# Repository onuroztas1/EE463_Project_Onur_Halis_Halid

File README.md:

# EE463_Project_Onur_Halis_Halid

Google Docs Link:
https://docs.google.com/document/d/1aUbiogccKc2OzVAZYlh6jZ1xVPGB8dJCKc63r1MVhF4/edit?usp=sharing

Google Slides Link:
https://docs.google.com/presentation/d/1uwI3XgHL8aJ05a1YgI6h8vrzoWMBWJBdzZAcA0tdUn0/edit?usp=sharing

Final Report Link: https://docs.google.com/document/d/186Mo9F-AtZxF1AbLLBHefO2YgB5pBUfvJb4pfUX1ARI/edit?usp=sharing

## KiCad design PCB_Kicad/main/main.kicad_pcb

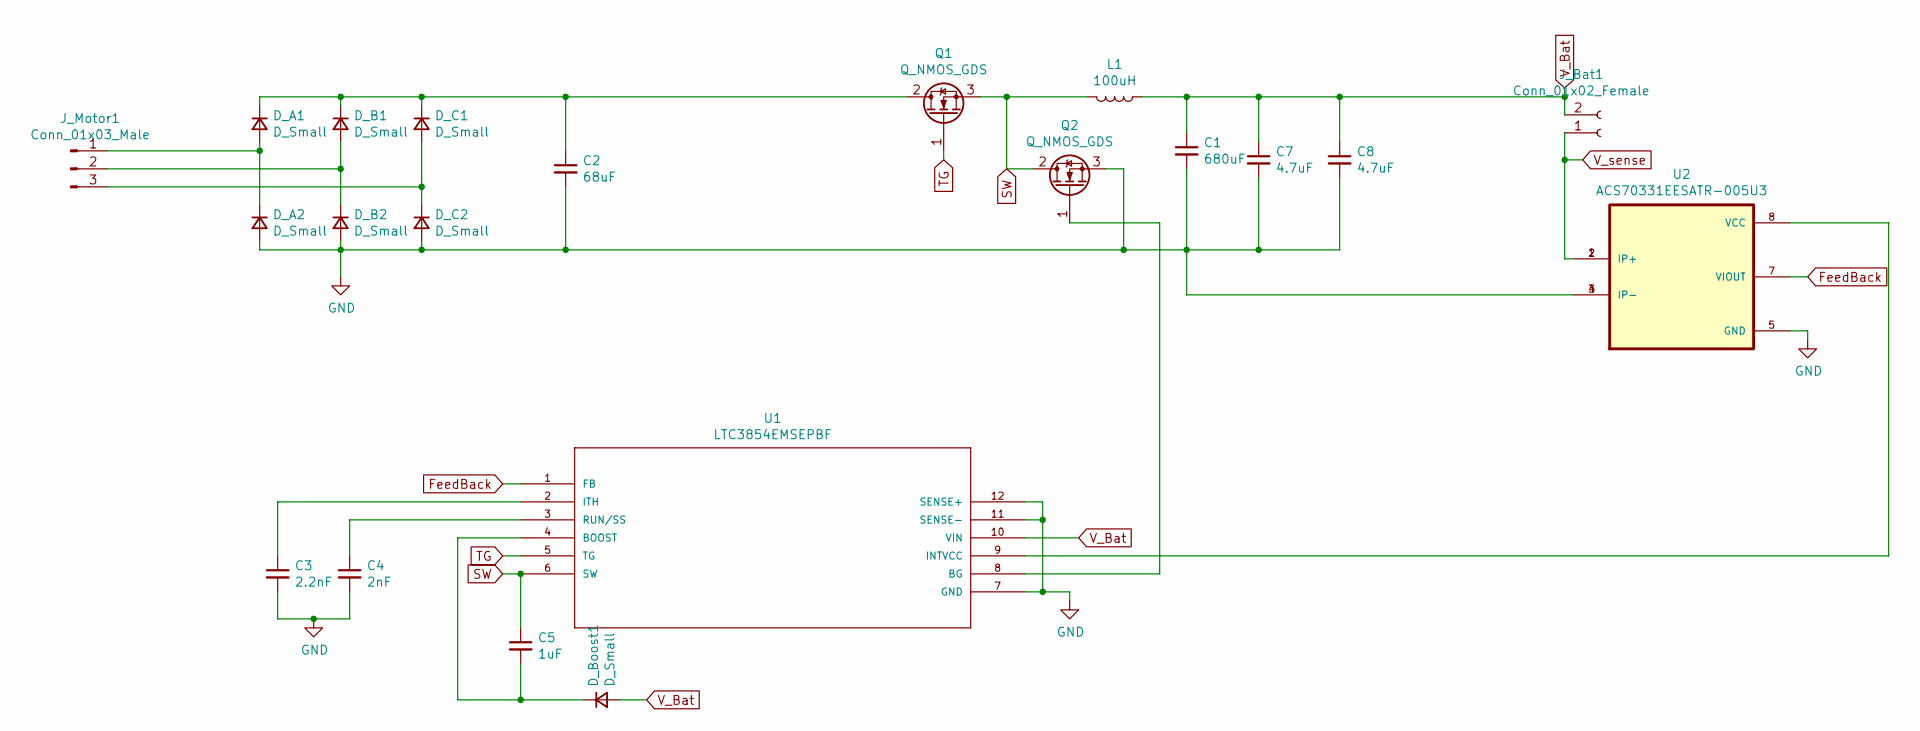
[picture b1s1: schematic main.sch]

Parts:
C1: 680uF; CP_Elec_10x7.9
C2: 68uF; CP_Radial_D18.0mm_P7.50mm
C3: 2.2nF; C_1206_3216Metric
C4: 2nF; C_1206_3216Metric
C5: 1uF; CP_Elec_8x10
C7, C8: 4.7uF; C_0805_2012Metric
D_A1, D_A2: D_Small; D_SMB
D_B1, D_B2: D_Small; D_SMB
D_Boost1: D_Small; D_SMB
D_C1, D_C2: D_Small; D_SMB
J_Bat1: Conn_01x02_Female; TerminalBlock_Altech_AK300-2_P5.00mm
J_Motor1: Conn_01x03_Male; TerminalBlock_Altech_AK300-3_P5.00mm
L1: 100uH; L_Wuerth_HCM-1390
Q1, Q2: Q_NMOS_GDS; TO-220-3_Vertical
U1: LTC3854EMSEPBF; MSOP-12-1EP_3x4mm_P0.65mm_EP1.65x2.85mm; MANUFACTURER_PART_NUMBER ltc3854emse#pbf
U2: ACS70331EESATR-005U3; SOIC-8-1EP_3.9x4.9mm_P1.27mm_EP2.29x3mm; PARTREV 2

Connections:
FeedBack: U1.1 (FB), U2.7 (VIOUT)
GND: C1.2, C2.2, C3.2, C4.2, C7.2, C8.2, D_A2.2 (A), D_B2.2 (A), D_C2.2 (A), Q2.3 (S), U1.7 (GND), U1.11 (SENSE-), U1.12 (SENSE+), U2.3 (IP-), U2.4 (IP-), U2.5 (GND)
unnamed: C2.1, D_A1.1 (K), D_B1.1 (K), D_C1.1 (K), Q1.2 (D)
unnamed: C3.1, U1.2 (ITH)
unnamed: C4.1, U1.3 (RUN/SS)
unnamed: C5.2, D_Boost1.1 (K), U1.4 (BOOST)
unnamed: D_A1.2 (A), D_A2.1 (K), J_Motor1.1
unnamed: D_B1.2 (A), D_B2.1 (K), J_Motor1.2
unnamed: D_C1.2 (A), D_C2.1 (K), J_Motor1.3
unnamed: Q2.1 (G), U1.8 (BG)
unnamed: U1.9 (INTVCC), U2.8 (VCC)
SW: C5.1, L1.2, Q1.3 (S), Q2.2 (D), U1.6 (SW)
TG: Q1.1 (G), U1.5 (TG)
V_Bat: C1.1, C7.1, C8.1, D_Boost1.2 (A), J_Bat1.2, L1.1, U1.10 (VIN)
V_sense: J_Bat1.1, U2.1 (IP+), U2.2 (IP+)

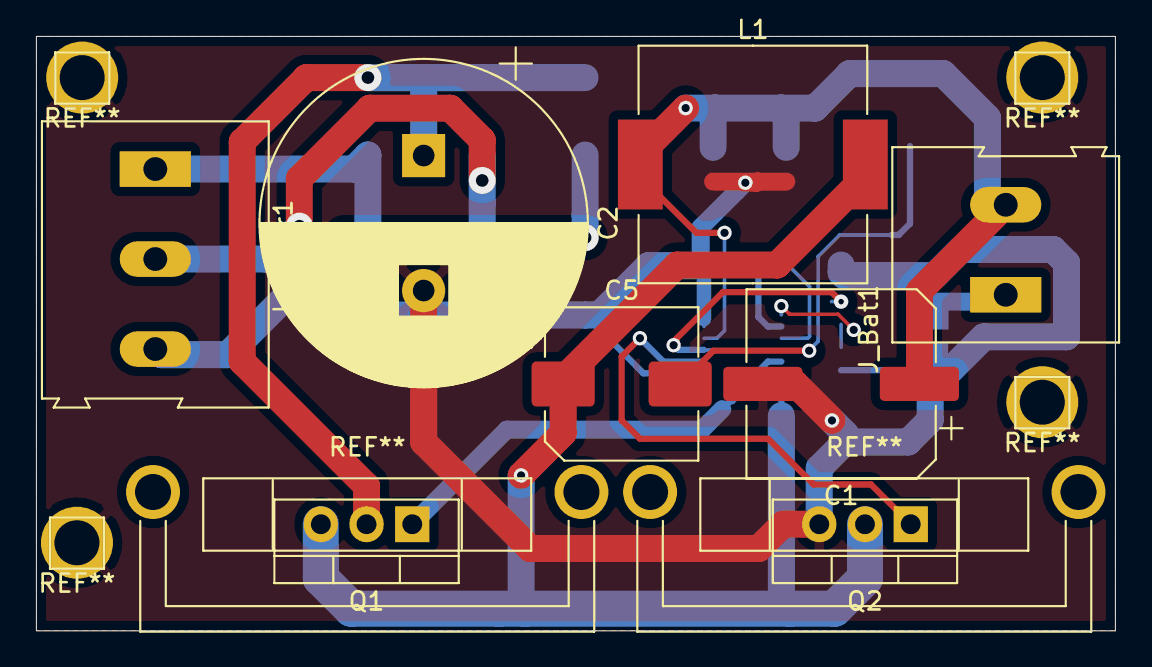
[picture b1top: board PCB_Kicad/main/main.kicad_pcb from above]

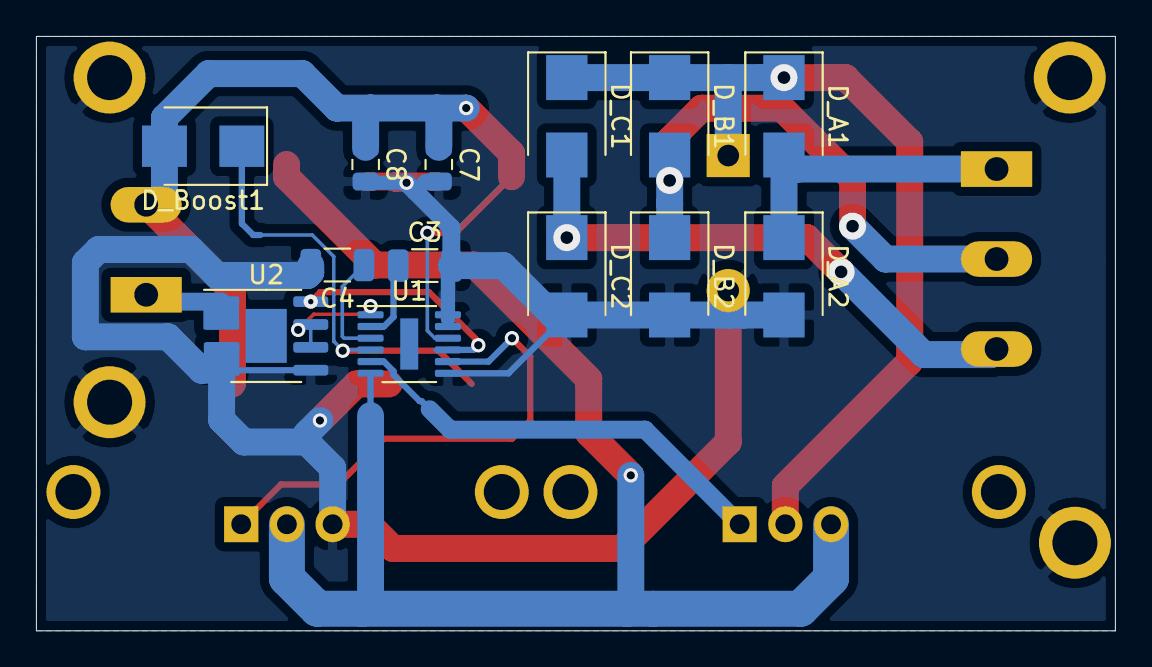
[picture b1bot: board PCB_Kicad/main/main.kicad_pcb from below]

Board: 2 copper layers, 59.9 x 33.0 mm, 21 parts (13 on the bottom side), 15 nets.

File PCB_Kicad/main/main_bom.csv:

"Source:","C:\Users\karab\OneDrive\Documents\GitHub\EE463_Project_Onur_Halis_Halid\PCB_Kicad\main\main.sch"
"Date:","12.01.2021 22:29:58"
"Tool:","Eeschema (5.1.8)-1"
"Component Count:","22"
"Ref","Value","Footprint","Datasheet","Manufacturer","Vendor"
"C1","680uF","Capacitor_SMD:CP_Elec_6.3x7.7","~","",""
"C2","68uF","Capacitor_SMD:CP_Elec_6.3x7.7","~","",""
"C3","2.2nF","Capacitor_SMD:C_1206_3216Metric","~","",""
"C4","2nF","Capacitor_SMD:C_1206_3216Metric","~","",""
"C5","1uF","Capacitor_SMD:CP_Elec_6.3x7.7","~","",""
"C6","68uF","Capacitor_SMD:CP_Elec_6.3x7.7","~","",""
"C7","4.7uF","Capacitor_SMD:C_2225_5664Metric_Pad1.80x6.60mm_HandSolder","~","",""
"C8","4.7uF","Capacitor_SMD:C_2225_5664Metric_Pad1.80x6.60mm_HandSolder","~","",""
"D_A1","D_Small","Diode_SMD:D_SMB","~","",""
"D_A2","D_Small","Diode_SMD:D_SMB","~","",""
"D_B1","D_Small","Diode_SMD:D_SMB","~","",""
"D_B2","D_Small","Diode_SMD:D_SMB","~","",""
"D_Boost1","D_Small","Diode_SMD:D_SMB","~","",""
"D_C1","D_Small","Diode_SMD:D_SMB","~","",""
"D_C2","D_Small","Diode_SMD:D_SMB","~","",""
"J_Bat1","Conn_01x02_Female","TerminalBlock:TerminalBlock_Altech_AK300-2_P5.00mm","~","",""
"J_Motor1","Conn_01x03_Male","TerminalBlock:TerminalBlock_Altech_AK300-3_P5.00mm","~","",""
"L1","100uH","Inductor_SMD:L_Wuerth_HCM-1390","~","",""
"Q1","Q_NMOS_GDS","Package_TO_SOT_THT:TO-220-3_Vertical","~","",""
"Q2","Q_NMOS_GDS","Package_TO_SOT_THT:TO-220-3_Vertical","~","",""
"U1","LTC3854EMSEPBF","Package_SO:MSOP-12-1EP_3x4mm_P0.65mm_EP1.65x2.85mm","","",""
"U2","ACS70331EESATR-005U3","Package_SO:SOIC-8-1EP_3.9x4.9mm_P1.27mm_EP2.29x3mm","","",""

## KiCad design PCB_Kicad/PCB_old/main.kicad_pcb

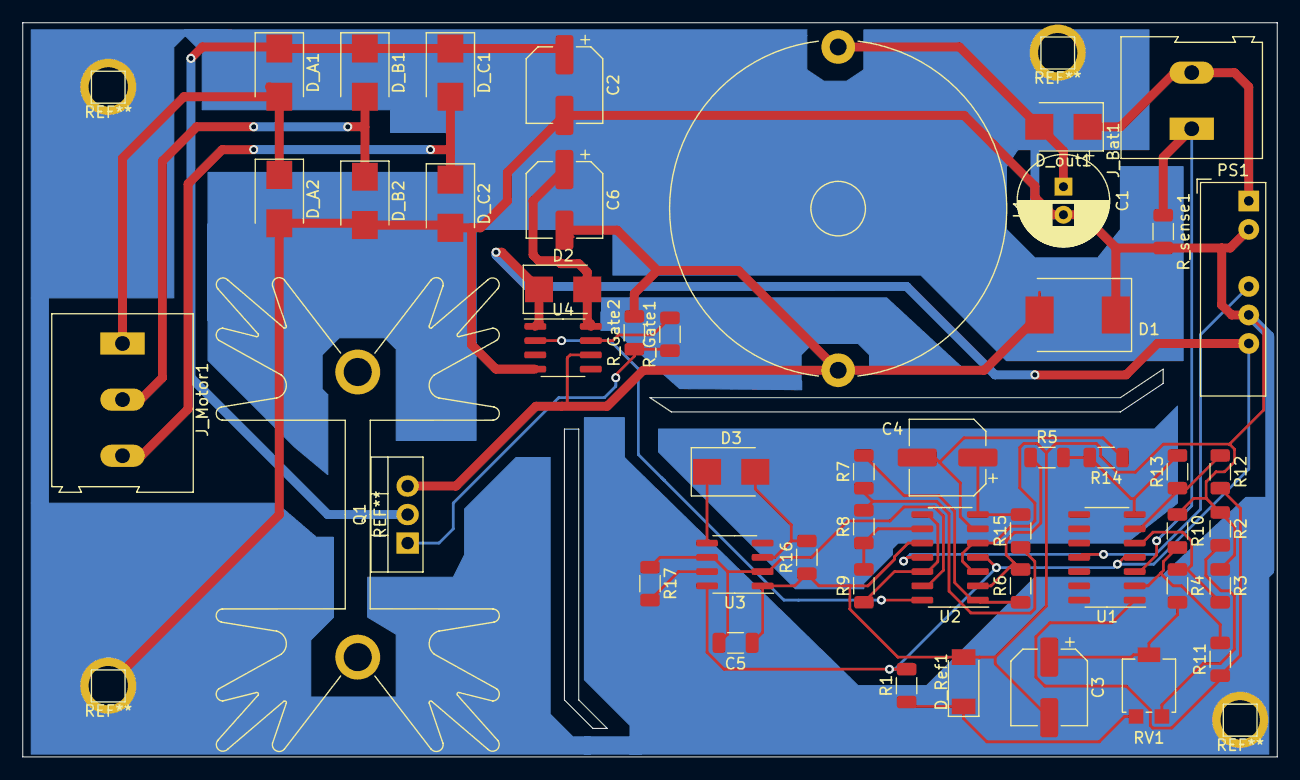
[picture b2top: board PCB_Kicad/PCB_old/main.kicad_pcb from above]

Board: 2 copper layers, 111.8 x 65.4 mm, 47 parts (0 on the bottom side), 34 nets.

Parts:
C1: 1mF; CP_Radial_D8.0mm_P2.50mm
C2: 100uF; CP_Elec_6.3x7.7
C3, C4, C6: C_Small; CP_Elec_6.3x7.7
C5: C_Small; C_1206_3216Metric
D1: DIODE; D_SMC
D2, D3: DIODE; D_SMB
D_A1, D_A2: D_Small; D_SMB
D_B1, D_B2: D_Small; D_SMB
D_C1, D_C2: D_Small; D_SMB
D_Ref1: D_Zener_Small; D_SOD-128
D_out1: D_Schottky; D_SMB
J_Bat1: Conn_01x02_Female; TerminalBlock_Altech_AK300-2_P5.00mm
J_Motor1: Conn_01x03_Male; TerminalBlock_Altech_AK300-3_P5.00mm
L1: L; L_Radial_D29.8mm_P28.80mm_muRATA_1400series
PS1: IA2412S; Converter_DCDC_XP_POWER-IAxxxxS_THT
Q1: Q_NMOS_GDS; TO-220-3_Vertical
R1, R2, R3, R4, R5, R6, R7, R8, R9, R10, R11, R12, R13, R14, R15, R16, R17: R_Small_US; R_1206_3216Metric
RV1: R_POT_TRIM_US; Potentiometer_Bourns_3314G_Vertical
R_Gate1, R_Gate2: R_Small_US; R_1206_3216Metric
R_sense1: R_Small_US; R_1206_3216Metric
U1, U2: TL084; SOIC-14_3.9x8.7mm_P1.27mm
U3: NA555D; SOIC-8_3.9x4.9mm_P1.27mm
U4: FAN7371; SOIC-8_3.9x4.9mm_P1.27mm

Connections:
+12V: D2.1, PS1.6, R1.2, U1.4, U2.4, U3.8, U4.1
-12V: PS1.4, U1.11, U2.11
GND: C1.2, C2.2, C3.2, C5.1, D1.1, D_A2.2, D_B2.2, D_C2.2, D_Ref1.2, PS1.2, PS1.5, R2.1, R3.1, R10.1, R16.1, R_sense1.2, U2.3, U2.5, U2.10, U3.1, U4.4
unnamed: C1.1, D_out1.2, L1.1
unnamed: C2.1, D_A1.1, D_B1.1, D_C1.1, Q1.2
unnamed: C3.1, R4.2, RV1.2
unnamed: C4.1, R15.2, U2.7
unnamed: C4.2, R14.1, U2.6
unnamed: C6.1, D2.2, U4.8
unnamed: C6.2, D1.2, L1.2, Q1.3, R_Gate2.2, U4.6
unnamed: D3.1, U3.5
unnamed: D3.2, R16.2, U3.3
unnamed: D_A1.2, D_A2.1, J_Motor1.1
unnamed: D_B1.2, D_B2.1, J_Motor1.2
unnamed: D_C1.2, D_C2.1, J_Motor1.3
unnamed: D_Ref1.1, R1.1, RV1.1
unnamed: Q1.1, R_Gate1.1, R_Gate2.1
unnamed: R2.2, RV1.3
unnamed: R3.2, R4.1, U1.5
unnamed: R5.1, R6.2, U2.2
unnamed: R6.1, R7.2, U2.1
unnamed: R8.1, R9.2, U2.9
unnamed: R9.1, U2.8, U2.12
unnamed: R10.2, R11.2, U1.2
unnamed: R11.1, R12.2, U1.1
unnamed: R12.1, R13.1, U1.6
unnamed: R5.2, R13.2, R14.2, U1.7
unnamed: R7.1, R8.2, R15.1
unnamed: R17.2, U3.7
unnamed: R_Gate1.2, U4.7
PWM_Gen: U2.14, U4.2
PWM_REF: C5.2, R17.1, U2.13, U3.2, U3.6
V_Bat: D_out1.1, J_Bat1.2, PS1.1
V_sense: J_Bat1.1, R_sense1.1, U1.3

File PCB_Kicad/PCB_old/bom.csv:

Column1;Column2;Column3;Column4;Column5;Column6
Source:;C:\Users\karab\OneDrive\Documents\GitHub\EE463_Project_Onur_Halis_Halid\PCB_Kicad\main\main.sch;;;;
Date:;24.12.2020 21:12:40;;;;
Tool:;Eeschema (5.1.8)-1;;;;
Component Count:;47;;;;
Ref;Value;Footprint;Datasheet;Manufacturer;Vendor
C1;1mF;Capacitor_THT:CP_Radial_D8.0mm_P2.50mm;~;;
C2;100uF;Capacitor_SMD:CP_Elec_6.3x7.7;~;;
C3;C_Small;Capacitor_SMD:CP_Elec_6.3x7.7;~;;
C4;C_Small;Capacitor_SMD:CP_Elec_6.3x7.7;~;;
C5;C_Small;Capacitor_SMD:C_1206_3216Metric;~;;
C6;C_Small;Capacitor_SMD:CP_Elec_6.3x7.7;~;;
D1;DIODE;Diode_SMD:D_SMC;https://www.taiwansemi.com/assets/uploads/datasheet/S12GC%20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;;
D2;DIODE;Diode_SMD:D_SMB;~;;
D3;DIODE;Diode_SMD:D_SMB;~;;
D_A1;D_Small;Diode_SMD:D_SMB;~;;
D_A2;D_Small;Diode_SMD:D_SMB;~;;
D_B1;D_Small;Diode_SMD:D_SMB;~;;
D_B2;D_Small;Diode_SMD:D_SMB;~;;
D_C1;D_Small;Diode_SMD:D_SMB;~;;
D_C2;D_Small;Diode_SMD:D_SMB;~;;
D_out1;D_Schottky;Diode_SMD:D_SMB;~;;
D_Ref1;D_Zener_Small;Diode_SMD:D_SOD-128;~;;
J_Bat1;Conn_01x02_Female;TerminalBlock:TerminalBlock_Altech_AK300-2_P5.00mm;~;;
J_Motor1;Conn_01x03_Male;TerminalBlock:TerminalBlock_Altech_AK300-3_P5.00mm;~;;
L1;L;Inductor_THT:L_Radial_D29.8mm_P28.80mm_muRATA_1400series;~;;
PS1;IA2412S;Converter_DCDC:Converter_DCDC_XP_POWER-IAxxxxS_THT;https://www.xppower.com/pdfs/SF_IA.pdf;;
Q1;Q_NMOS_GDS;Package_TO_SOT_THT:TO-220-3_Vertical;~;;
R1;R_Small_US;Resistor_SMD:R_1206_3216Metric;~;;
R2;R_Small_US;Resistor_SMD:R_1206_3216Metric;~;;
R3;R_Small_US;Resistor_SMD:R_1206_3216Metric;~;;
R4;R_Small_US;Resistor_SMD:R_1206_3216Metric;~;;
R5;R_Small_US;Resistor_SMD:R_1206_3216Metric;~;;
R6;R_Small_US;Resistor_SMD:R_1206_3216Metric;~;;
R7;R_Small_US;Resistor_SMD:R_1206_3216Metric;~;;
R8;R_Small_US;Resistor_SMD:R_1206_3216Metric;~;;
R9;R_Small_US;Resistor_SMD:R_1206_3216Metric;~;;
R10;R_Small_US;Resistor_SMD:R_1206_3216Metric;~;;
R11;R_Small_US;Resistor_SMD:R_1206_3216Metric;~;;
R12;R_Small_US;Resistor_SMD:R_1206_3216Metric;~;;
R13;R_Small_US;Resistor_SMD:R_1206_3216Metric;~;;
R14;R_Small_US;Resistor_SMD:R_1206_3216Metric;~;;
R15;R_Small_US;Resistor_SMD:R_1206_3216Metric;~;;
R16;R_Small_US;Resistor_SMD:R_1206_3216Metric;~;;
R17;R_Small_US;Resistor_SMD:R_1206_3216Metric;~;;
R_Gate1;R_Small_US;Resistor_SMD:R_1206_3216Metric;~;;
R_Gate2;R_Small_US;Resistor_SMD:R_1206_3216Metric;~;;
R_sense1;R_Small_US;Resistor_SMD:R_1206_3216Metric;~;;
RV1;R_POT_TRIM_US;Potentiometer_SMD:Potentiometer_Bourns_3314G_Vertical;~;;
U1;TL084;Package_SO:SOIC-14_3.9x8.7mm_P1.27mm;http://www.ti.com/lit/ds/symlink/tl081.pdf;;
U2;TL084;Package_SO:SOIC-14_3.9x8.7mm_P1.27mm;http://www.ti.com/lit/ds/symlink/tl081.pdf;;
U3;NA555D;Package_SO:SOIC-8_3.9x4.9mm_P1.27mm;http://www.ti.com/lit/ds/symlink/ne555.pdf;;
U4;FAN7371;Package_SO:SOIC-8_3.9x4.9mm_P1.27mm;https://www.onsemi.com/pub/Collateral/FAN7371-D.pdf;;

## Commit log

2020-12-08 Initial design model
    Basic full bridge diode rectifier and buck converter with openloop duty cycle.
2020-12-08 Initial design with closed loop control
    First closed loop control is created. Batterry current is with in given limitations. Howerver controller must be adjusted. Analog design of the controller is also absent in this design.
2020-12-13 test
2020-12-13 Analog buck converter
    FBDR with analog controlled closed loop buck converter. PI controller is implemented with opamps. Ramp function for PWM signal is created using 555 timer. Frequency is changed to 12.5Khz because of r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
2020-12-20 Uptaded design
2020-12-20 ltspice file for IC buck
2020-12-21 possible components
2020-12-22 pcb drawings
2020-12-22 components
2020-12-22 PWM test circuit for MOS driving with IL as input
2020-12-22 Gate driver IC is selected and prepared a circuit for Buck Converters nmos gate
2020-12-23 components and spice model
2020-12-23 Final design model and component links
2020-12-23 Comments on topology selection, will add some figures etc.
2020-12-24 Added calculations and Figure
2020-12-24 test file for topology document
2020-12-24 some figures form simulink
2020-12-24 kicad drawings update
2020-12-24 files created
2020-12-24 bom created
2020-12-25 update bom
2021-01-01 ic tested
2021-01-12 Final Report Link!
2021-01-12 kicad update
2021-01-12 simulation from ltspice
2021-01-12 model update
2021-01-14 kicad_updated
2021-01-14 heat_anlysis_done
2021-01-14 pcb_images
2021-01-14 final simulink model
2021-01-15 Siemens NX Case design
2021-01-15 Rectifier voltage simulation
2021-01-15 LTspice simulation model
2021-01-15 final report added
